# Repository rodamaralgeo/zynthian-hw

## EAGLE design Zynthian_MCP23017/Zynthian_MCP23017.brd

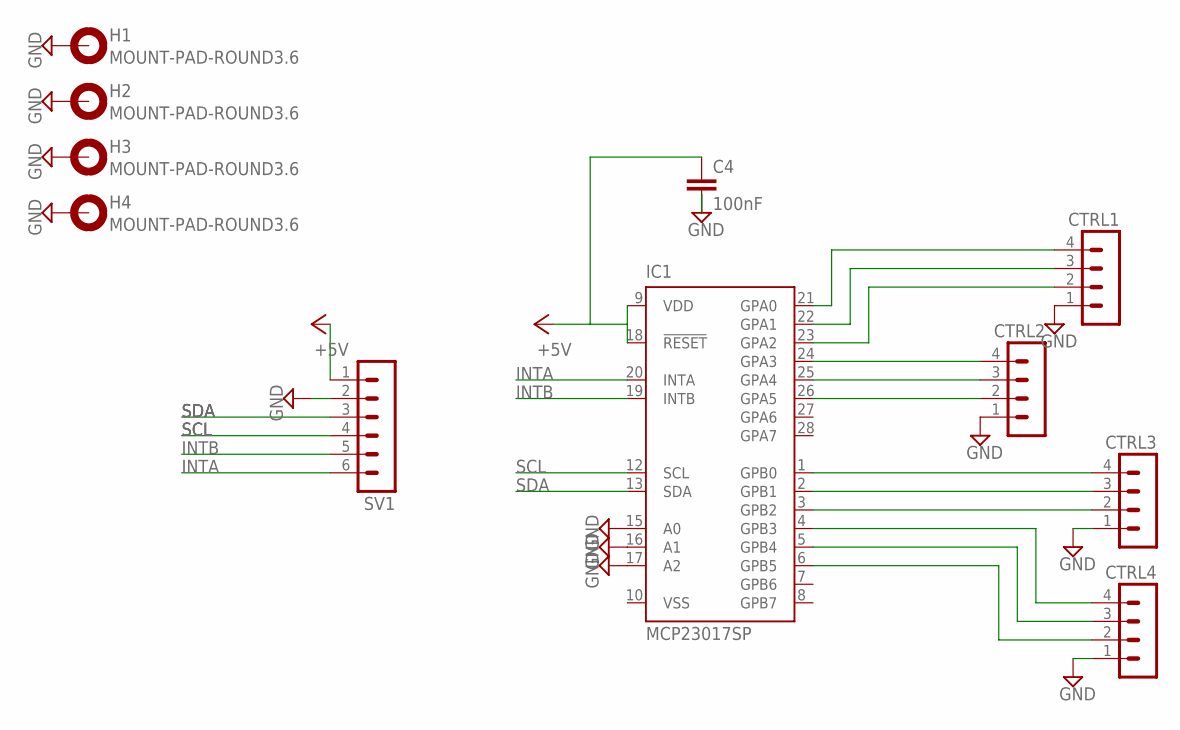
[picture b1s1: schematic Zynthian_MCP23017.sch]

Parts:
C4: 100nF; 072X025
CTRL1, CTRL2, CTRL3, CTRL4: MA04-1
H1, H2, H3, H4: MOUNT-PAD-ROUND3.6; 3,6-PAD
IC1: MCP23017SP; DIL28-3
SV1: MA06-1

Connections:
+5V: C4.1, IC1.9 (VDD), IC1.18 (!RESET), SV1.1
GND: C4.2, CTRL1.1, CTRL2.1, CTRL3.1, CTRL4.1, H1.B3,6, H2.B3,6, H3.B3,6, H4.B3,6, IC1.15 (A0), IC1.16 (A1), IC1.17 (A2), SV1.2
INTA: IC1.20 (INTA), SV1.6
INTB: IC1.19 (INTB), SV1.5
unnamed: CTRL1.4, IC1.21 (GPA0)
unnamed: CTRL1.3, IC1.22 (GPA1)
unnamed: CTRL1.2, IC1.23 (GPA2)
unnamed: CTRL2.4, IC1.24 (GPA3)
unnamed: CTRL2.3, IC1.25 (GPA4)
unnamed: CTRL2.2, IC1.26 (GPA5)
unnamed: CTRL3.4, IC1.1 (GPB0)
unnamed: CTRL3.3, IC1.2 (GPB1)
unnamed: CTRL3.2, IC1.3 (GPB2)
unnamed: CTRL4.4, IC1.4 (GPB3)
unnamed: CTRL4.3, IC1.5 (GPB4)
unnamed: CTRL4.2, IC1.6 (GPB5)
SCL: IC1.12 (SCL), SV1.4
SDA: IC1.13 (SDA), SV1.3
VSS: IC1.10 (VSS)

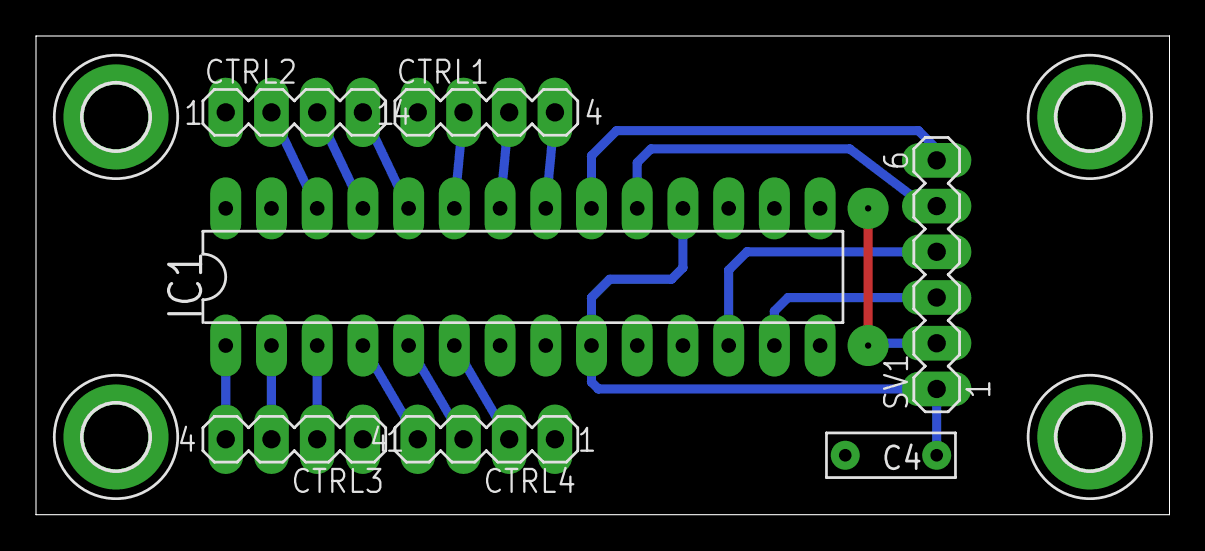
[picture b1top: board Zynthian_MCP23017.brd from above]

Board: 2 copper layers, 63.0 x 26.6 mm, 11 parts (0 on the bottom side), 18 nets.

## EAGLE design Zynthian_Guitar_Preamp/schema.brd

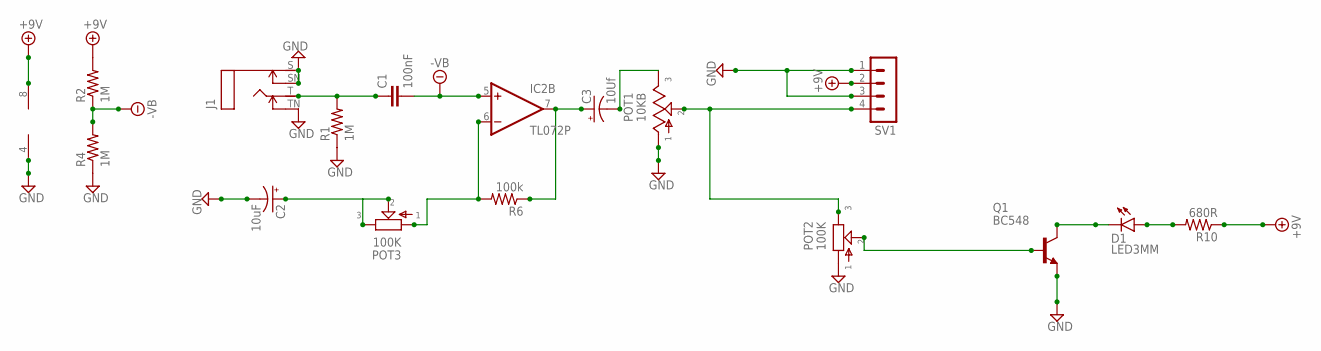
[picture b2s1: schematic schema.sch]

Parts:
C1: 100nF; 072X035
C2: 10uF; 050_020_1
C3: 10Uf; 050_020_1
D1: LED3MM
IC2: TL072P; DIL08
J1: MONOSWS; NMJ4HC-S
POT1: 10KB; 16MM-PCB-MOUNT
POT2, POT3: 100K; B25P
Q1: BC548; TO92-EBC
R1, R2, R4: 1M; R0207/3
R6: 100k; R0207/1V
R10: 680R; R0207/3
SV1: MA04-1

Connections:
+9V: IC2.8 (V+), R2.2, R10.1, SV1.2
-VB: C1.2, IC2.5 (+IN), R2.1, R4.2
GND: C2.-, IC2.4 (V-), J1.S, J1.SN, J1.TN, POT1.1, POT2.1, Q1.E, R1.1, R4.1, SV1.1, SV1.3
unnamed: C1.1, J1.T, R1.2
unnamed: IC2.6 (-IN), POT3.1, R6.2
unnamed: C3.-, POT1.3
unnamed: D1.A, R10.2
unnamed: C2.+, POT3.2, POT3.3
unnamed: D1.K (C), Q1.C
unnamed: C3.+, IC2.7 (OUT), R6.1
unnamed: POT1.2, POT2.3, SV1.4
unnamed: POT2.2, Q1.B

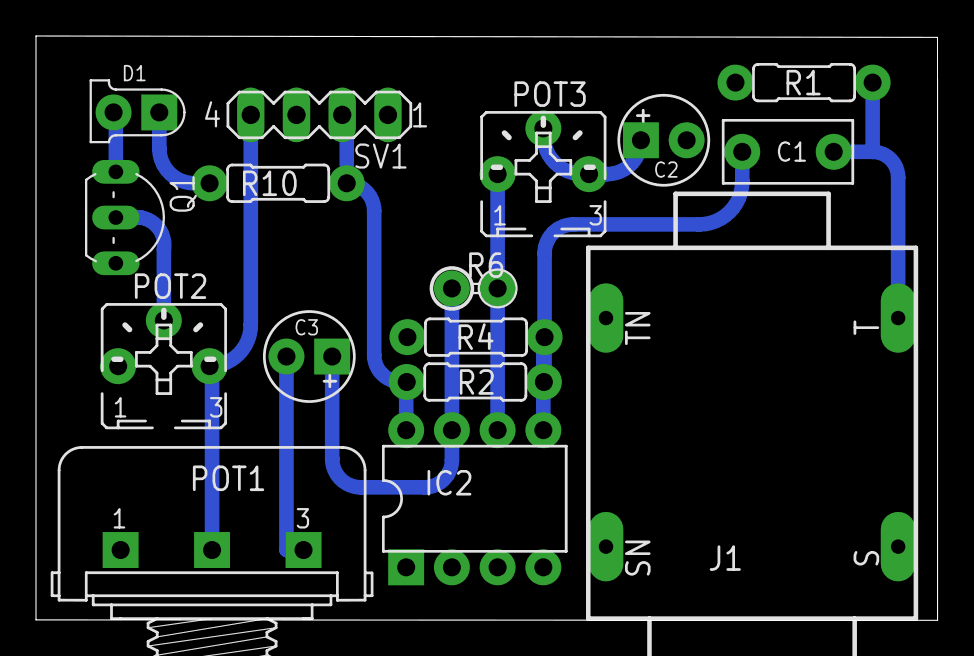
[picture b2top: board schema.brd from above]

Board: 2 copper layers, 50.1 x 32.5 mm, 16 parts (0 on the bottom side), 12 nets.
